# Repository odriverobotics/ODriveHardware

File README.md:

# ODriveHardware
This project is all about accuratly driving brushless motors, for cheap. The aim is to make it possible to use inexpensive brushless motors in high performance robotics projects.
Like this (click for video):

If you want to get your hands on a board, check out [this post](https://hackaday.io/project/11583-odrive-high-performance-motor-control/log/40702-boards-and-development).

This repository contains the circuit board design of ODrive. The other related repositories are:
* [ODriveFirmware](https://github.com/madcowswe/ODriveFirmware): Firmware that runs on the board.
* [ODrive](https://github.com/madcowswe/ODrive): Configuration and analysis scripts that runs on a PC.

There is also [ODriveFPGA](https://github.com/madcowswe/ODriveFPGA), which contains the FPGA logic and software that runs on the FPGA based ODrive. This is not currently in development, but may be resumed at some later date.

## Odrive v3 board
The pinout from the microcontroller to the board is documented [here](https://docs.google.com/spreadsheets/d/1QXDCs1IRtUyG__M_9WruWOheywb-GhOwFtfPcHuN2Fg/edit?usp=sharing).

### Pictures!

### ODrive v3.1 errata
* The silkscreen labels for the encoders (M0, M1) are reversed.
* The output impedence of the current amplifiers were not considered when designing the post-amplifier filters. Hence the response is about 5x slower than designed. Max allowed modulation index is therefore about 50%.

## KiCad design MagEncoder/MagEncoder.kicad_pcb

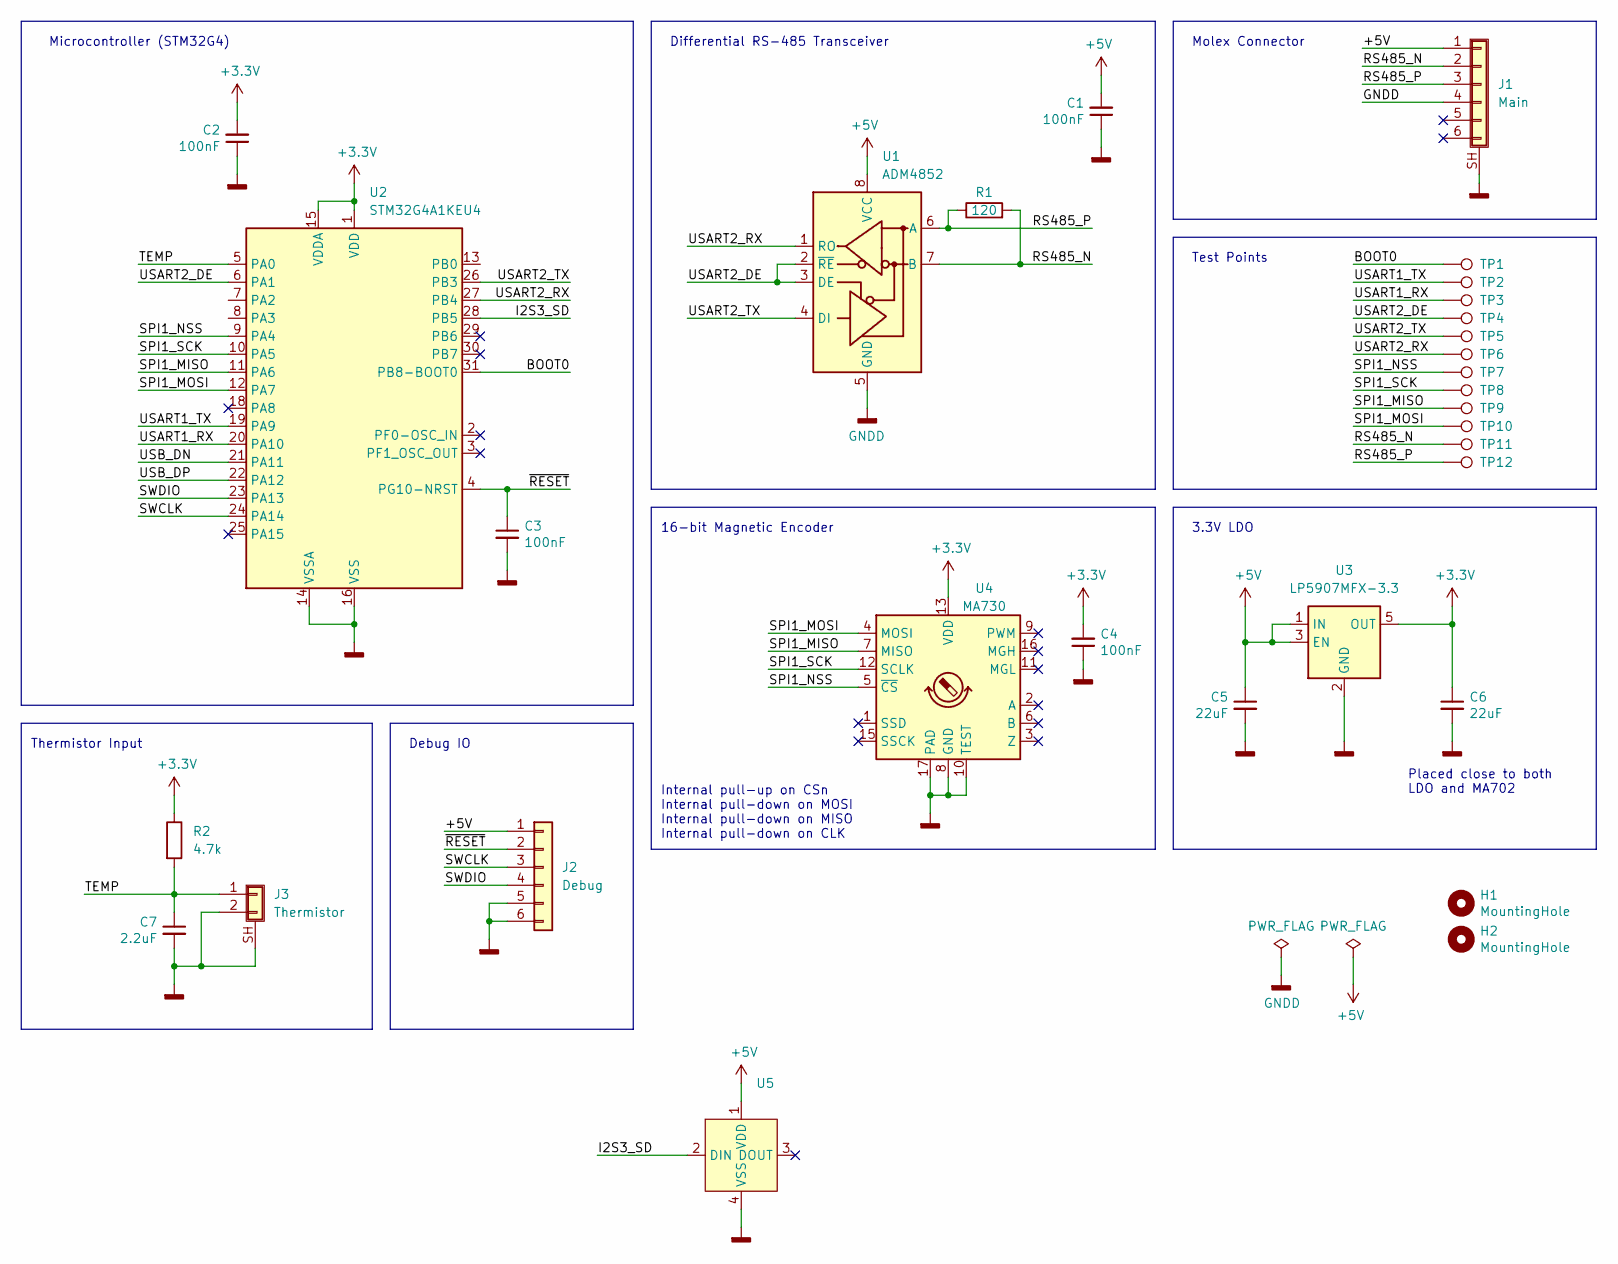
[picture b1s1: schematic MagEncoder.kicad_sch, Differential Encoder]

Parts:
C1, C2, C3, C4: 100nF; C_0402_1005Metric
C5, C6: 22uF; C_0805_2012Metric
C7: 2.2uF; C_0402_1005Metric
H1, H2: MountingHole; MountingHole_3mm
J1: Main; Molex_CLIK-Mate_502585-0670_1x06-1MP_P1.50mm_Horizontal
J2: Debug; Tag-Connect_TC2030-IDC-NL_2x03_P1.27mm_Vertical
J3: Thermistor; JST_GH_SM02B
R1: 120; R_0402_1005Metric
R2: 4.7k; R_0402_1005Metric
TP1, TP2, TP3, TP4, TP5, TP6, TP7, TP8, TP9, TP10, TP11, TP12: TestPoint; TestPoint_Pad_D1.0mm
U1: ADM4852; LFCSP-8-1EP_3x3mm_P0.5mm_EP1.45x1.74mm
U2: STM32G4A1KEU4; UFQFPN-32-1EP_5x5mm_P0.5mm_EP3.5x3.5mm
U3: LP5907MFX-3.3; SOT-23-5
U4: MA730; QFN-16-1EP_3x3mm_P0.5mm_EP1.7x1.7mm
U5: (no value)

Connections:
+3V3: C2.2, C4.2, C6.1, R2.1, U2.1 (VDD), U2.15 (VDDA), U2.17 (VDD), U3.5 (OUT), U4.13 (VDD)
+5V: C1.2, C5.1, J1.1, J2.1, U1.8 (VCC), U3.1 (IN), U3.3 (EN), U5.1 (VDD)
/BOOT0: TP1.1, U2.31 (PB8-BOOT0)
/I2S3_SD: U2.28 (PB5), U5.2 (DIN)
/RS485_N: J1.2, R1.2, TP11.1, U1.7 (B)
/RS485_P: J1.3, R1.1, TP12.1, U1.6 (A)
/SPI1_MISO: TP9.1, U2.11 (PA6), U4.7 (MISO)
/SPI1_MOSI: TP10.1, U2.12 (PA7), U4.4 (MOSI)
/SPI1_NSS: TP7.1, U2.9 (PA4), U4.5 (~CS)
/SPI1_SCK: TP8.1, U2.10 (PA5), U4.12 (SCLK)
/SWCLK: J2.3, U2.24 (PA14)
/SWDIO: J2.4, U2.23 (PA13)
/TEMP: C7.1, J3.1, R2.2, U2.5 (PA0)
/USART1_RX: TP3.1, U2.20 (PA10)
/USART1_TX: TP2.1, U2.19 (PA9)
/USART2_DE: TP4.1, U1.2 (~RE), U1.3 (DE), U2.6 (PA1)
/USART2_RX: TP6.1, U1.1 (RO), U2.27 (PB4)
/USART2_TX: TP5.1, U1.4 (DI), U2.26 (PB3)
/USB_DN: U2.21 (PA11)
/USB_DP: U2.22 (PA12)
/~RESET: C3.1, J2.2, U2.4 (PG10-NRST)
GNDD: C1.1, C2.1, C3.2, C4.1, C5.2, C6.2, C7.2, J1.4, J1.SH (Shield), J2.5, J2.6, J3.2, J3.SH (Shield), U1.5 (GND), U1.PAD, U2.14 (VSSA), U2.16 (VSS), U2.32 (VSS), U2.33 (PAD), U3.2 (GND), U4.8 (GND), U4.10 (TEST), U4.17 (PAD), U5.4 (VSS)

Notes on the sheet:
Test Points
Thermistor Input
Internal pull-up on CSn Internal pull-down on MOSI Internal pull-down on MISO Internal pull-down on CLK
16-bit Magnetic Encoder
Placed close to both LDO and MA702
3.3V LDO
Differential RS-485 Transceiver
Microcontroller (STM32G4)
Molex Connector
Debug IO

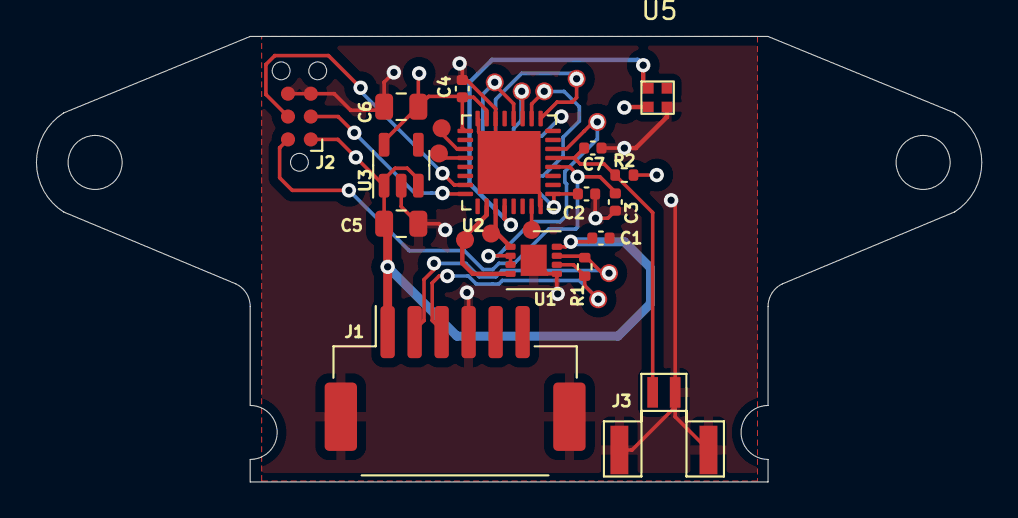
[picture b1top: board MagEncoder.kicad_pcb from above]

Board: 4 copper layers, 52.5 x 24.8 mm, 31 parts (1 on the bottom side), 20 nets.

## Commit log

2016-05-31 Hardware repository split
2016-05-31 Create LICENSE
2016-06-25 rename v3.0 bom saves
2016-06-25 Done with first round of fixes for v3.1
2016-07-24 add test probe 1x and 5x
2016-07-24 add schematic and bom
2016-07-24 clean out old outputs
2016-07-31 add USB testpoints
2016-12-02 schematic pdf and BOM updated to v3.1rc2 (add USB test points)
2017-01-13 Added More Documentation
    Added More Documumentation including a Produce_Documentation output job
    to make keeping the docs upto date much easier, and Assembly_BOM.PCBDwf.
    Documentaion.PDF is the output from Produce_Documentation
2017-01-23 Corrected Silk Screen Mistake ( M0 M1 Designators on Encoder inputs swapped)
2017-01-24 Maybe altium and git dont work well together...
2017-01-31 Add v3.1 errata to readme
2017-03-13 consolidate 0.1in headers
2017-03-22 Fix current filter values
2017-03-23 make analog testpoint breakout
2017-03-23 add precision LDO for AVCC
2017-03-25 add fiducials
2017-03-25 realign heatsink mounting holes
2017-03-25 improve labling
2017-03-25 change mosfets to more available version (NTMFS4935NT1G)
2017-03-25 add v3.2 docs
2017-03-26 remove unknown files
2017-04-19 update v3.2 changelog
2017-06-02 Add v3.2 STEP file
2017-06-08 flip cap and vreg, add secondary DC pads
2017-06-08 add power LED
2017-06-10 change terminal blocks to 7.62mm pitch
2017-06-10 remap GPIO pins, discard auxV
2017-06-17 increase encoder pullups to 3k3 for better compatibility with push-pull encoders
2017-06-17 added v3.3 docs
2017-06-17 update changelog
2017-09-04 add mechanical dimensions
2017-09-04 dimensions in mm
2017-11-04 fix ground issue, shunt via resistance
2017-11-07 Add 48V variation
2017-11-07 add 48V silkscreen
2018-01-26 add second shunt net-ties
2018-01-26 Move GVDD caps from PGND to GND
2018-06-07 add changelog for v3.5
2018-06-09 add v3.4 docs
2018-07-23 add v3.5 docs
2018-11-16 copy mech dims to v3.5
2020-03-30 Reset file so Altium changes IsFootprintSame parameter to the same.
2020-03-30 Update all component parameters from schematics
2020-03-31 All changes documented in v3/v3.4 changes/CHANGELOG.md
2020-03-31 Clean Schematics. NO COPPER CHANGES. All changes documented in v3/v3.4 changes/CHANGELOG.md
2020-04-01 Update to Odrive schematic Template
2022-05-13 Add MagEncoder
2022-05-13 Add RGB LED
